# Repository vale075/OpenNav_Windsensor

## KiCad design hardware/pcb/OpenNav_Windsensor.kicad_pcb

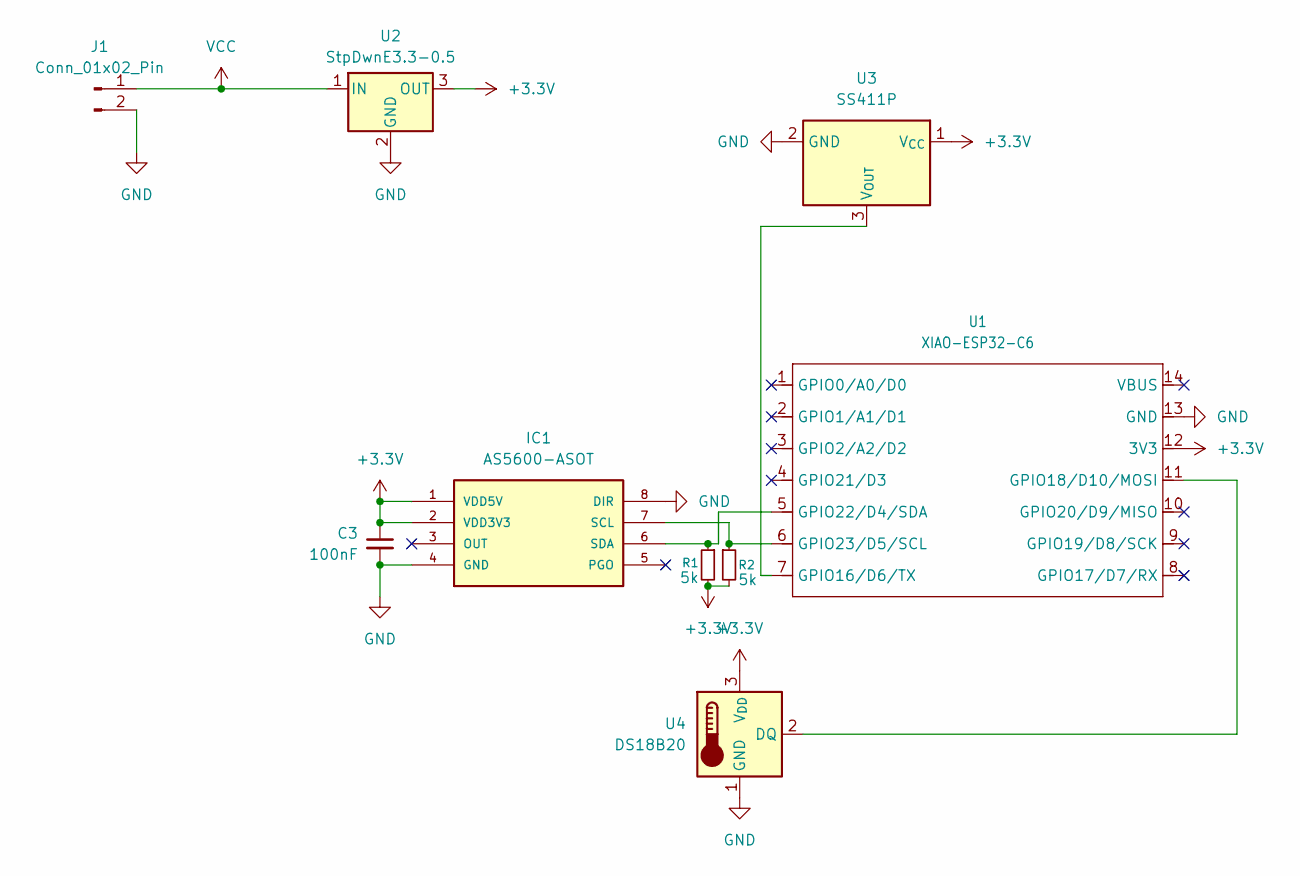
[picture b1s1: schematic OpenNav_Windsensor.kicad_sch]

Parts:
C3: 100nF; C_Disc_D7.5mm_W5.0mm_P10.00mm
IC1: AS5600-ASOT; SOIC127P600X175-8N; MOUSER_PART_NUMBER 985-AS5600-ASOT
J1: Conn_01x02_Pin; JST_XH_B2B-XH-A_1x02_P2.50mm_Vertical
R1, R2: 5k; R_Axial_DIN0207_L6.3mm_D2.5mm_P7.62mm_Horizontal
U1: XIAO-ESP32-C6; XIAO-ESP32C6-DIP
U2: StpDwnE3.3-0.5; CONV_R-78K3.3-0.5
U3: SS411P
U4: DS18B20; TO-92_Inline

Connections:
+3.3V: C3.1, IC1.1 (VDD5V), IC1.2 (VDD3V3), R1.2, R2.2, U1.12 (3V3), U2.3 (OUT), U3.1 (V_{CC}), U4.3 (V_{DD})
GND: C3.2, IC1.4 (GND), IC1.8 (DIR), J1.2, U1.13 (GND), U2.2 (GND), U3.2 (GND), U4.1 (GND)
unnamed: IC1.7 (SCL), R2.1, U1.6 (GPIO23/D5/SCL)
unnamed: IC1.6 (SDA), R1.1, U1.5 (GPIO22/D4/SDA)
unnamed: U1.7 (GPIO16/D6/TX), U3.3 (V_{OUT})
unnamed: U1.11 (GPIO18/D10/MOSI), U4.2 (DQ)
VCC: J1.1, U2.1 (IN)

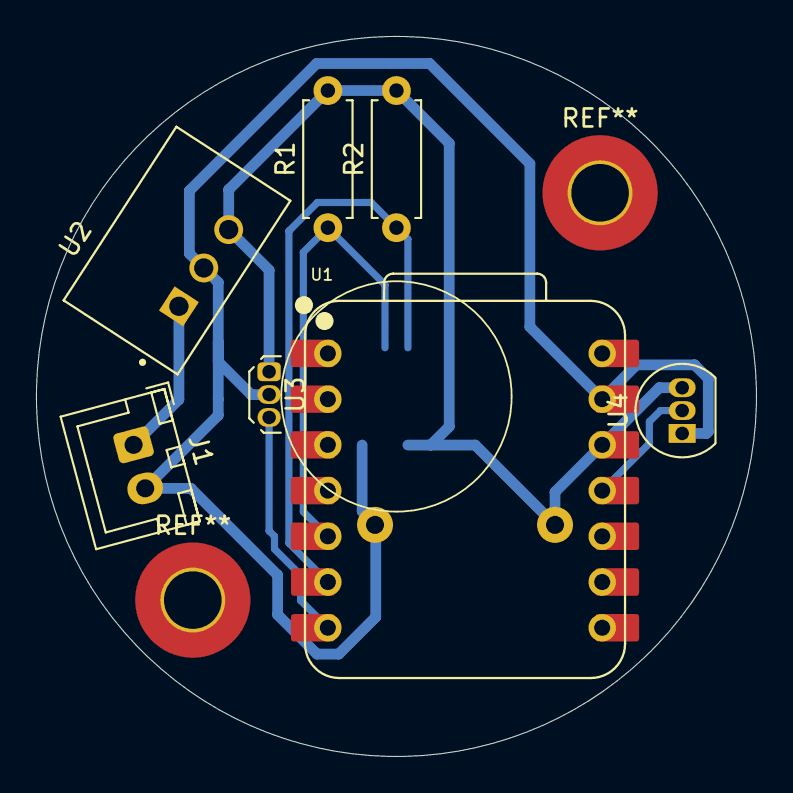
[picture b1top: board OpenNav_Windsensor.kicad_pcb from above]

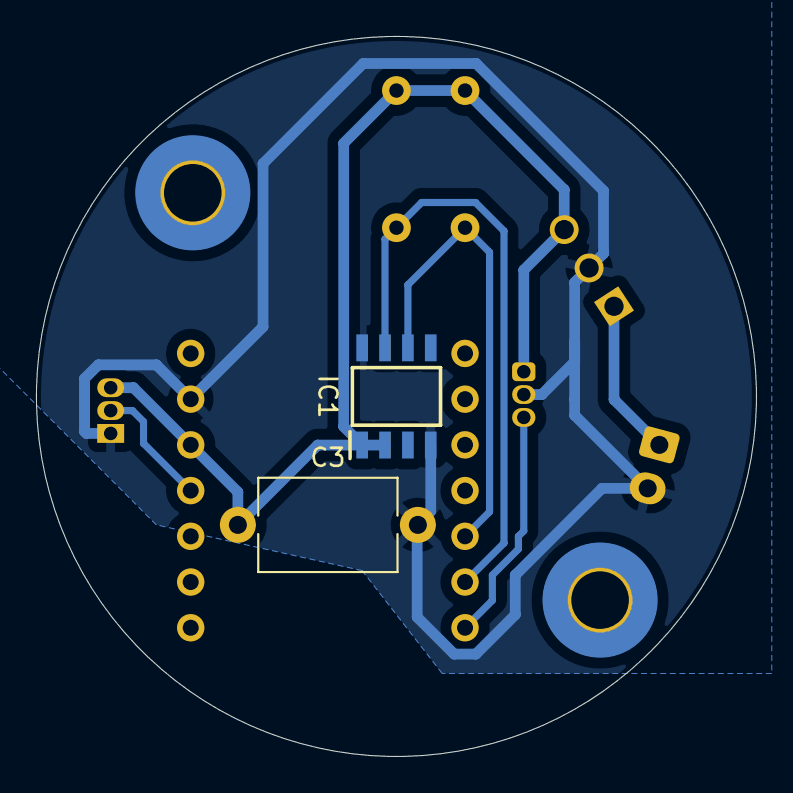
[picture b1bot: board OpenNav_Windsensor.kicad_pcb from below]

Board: 2 copper layers, 40.0 x 40.0 mm, 9 parts (2 on the bottom side), 7 nets.

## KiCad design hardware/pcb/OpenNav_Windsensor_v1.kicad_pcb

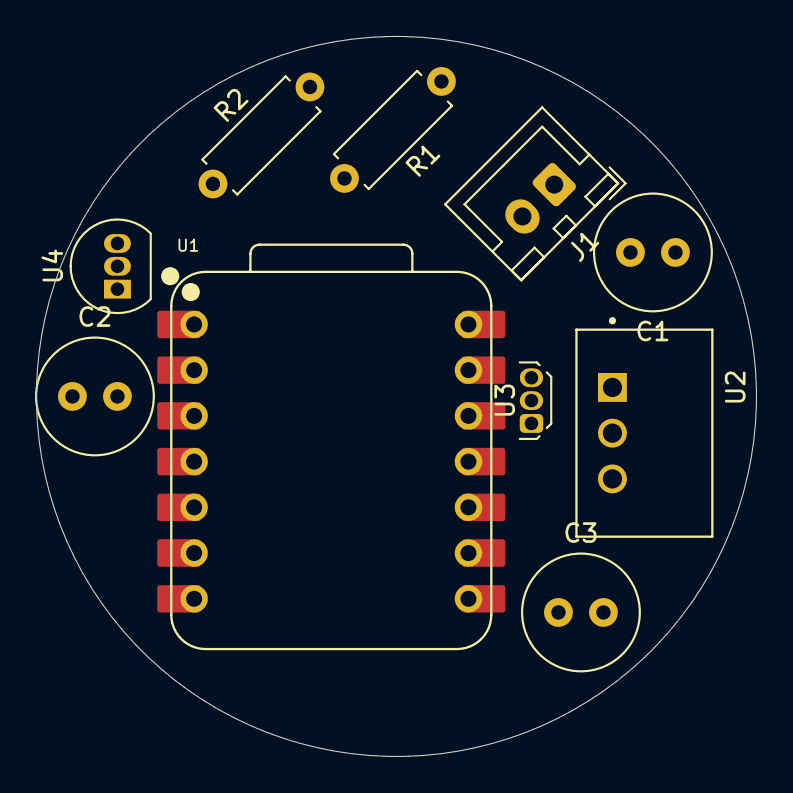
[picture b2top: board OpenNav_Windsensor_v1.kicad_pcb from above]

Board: 2 copper layers, 40.0 x 40.0 mm, 11 parts (1 on the bottom side), 7 nets, no tracks yet.

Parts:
C1: 10uF/50V; C_Radial_D6.3mm_H11.0mm_P2.50mm
C2: 20uF/10V; C_Radial_D6.3mm_H11.0mm_P2.50mm
C3: 100nF; C_Radial_D6.3mm_H11.0mm_P2.50mm
IC1: AS5600-ASOT; SOIC127P600X175-8N
J1: Conn_01x02_Pin; JST_XH_B2B-XH-A_1x02_P2.50mm_Vertical
R1, R2: 5k; R_Axial_DIN0207_L6.3mm_D2.5mm_P7.62mm_Horizontal
U1: XIAO-ESP32-C6; XIAO-ESP32C6-DIP
U2: StpDwnE3.3-0.5; CONV_R-78K3.3-0.5
U3: SS411P
U4: DS18B20; TO-92_Inline

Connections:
+3.3V: C2.1, C3.1, IC1.1 (VDD5V), IC1.2 (VDD3V3), R1.2, R2.2, U1.12 (3V3), U2.3 (OUT), U3.1 (V_{CC}), U4.3 (V_{DD})
GND: C1.2, C2.2, C3.2, IC1.4 (GND), IC1.8 (DIR), J1.2, U1.13 (GND), U2.2 (GND), U3.2 (GND), U4.1 (GND)
unnamed: IC1.7 (SCL), R2.1, U1.6 (GPIO23/D5/SCL)
unnamed: IC1.6 (SDA), R1.1, U1.5 (GPIO22/D4/SDA)
unnamed: U1.8 (GPIO17/D7/RX), U4.2 (DQ)
unnamed: U1.10 (GPIO20/D9/MISO), U3.3 (V_{OUT})
VCC: C1.1, J1.1, U2.1 (IN)

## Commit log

2025-09-14 init
2025-09-14 KiCAD gitignore added
2025-09-14 Schématique fait
2025-09-30 SMD V2
2025-10-02 Corrected capacitor size based on what bought
